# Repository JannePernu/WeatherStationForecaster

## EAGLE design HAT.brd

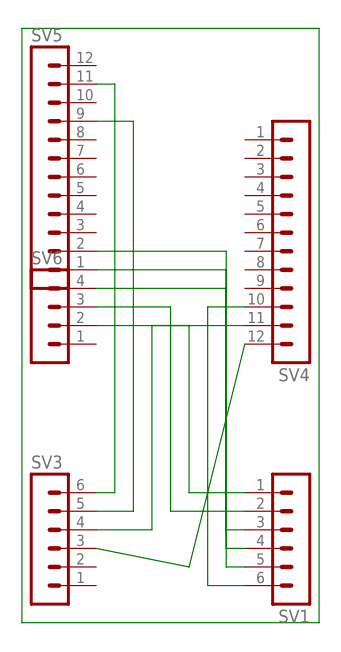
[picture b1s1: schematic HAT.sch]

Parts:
SV1, SV3: MA06-1
SV4, SV5: MA12-1
SV6: MA04-1

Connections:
unnamed: SV3.3, SV4.12
unnamed: SV3.4, SV4.11
unnamed: SV3.6, SV5.11
unnamed: SV3.5, SV5.9
unnamed: SV1.1, SV6.2
unnamed: SV1.2, SV6.3
unnamed: SV1.3, SV6.4
unnamed: SV1.4, SV5.1
unnamed: SV1.5, SV5.2
unnamed: SV1.6, SV4.10

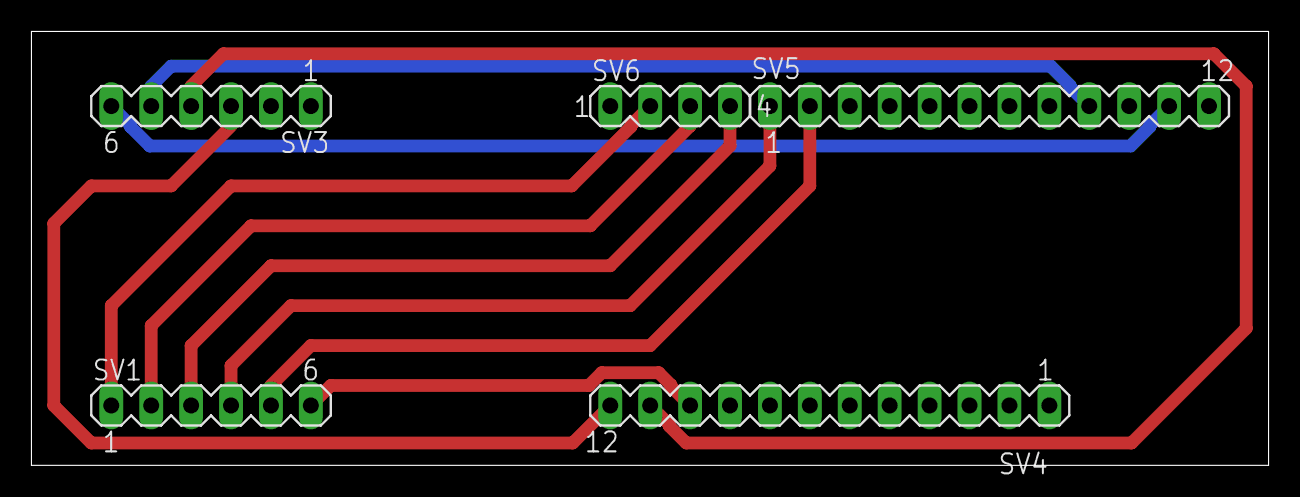
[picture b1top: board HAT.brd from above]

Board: 2 copper layers, 78.7 x 27.6 mm, 5 parts (0 on the bottom side), 10 nets.
